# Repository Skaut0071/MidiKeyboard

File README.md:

# MidiKeyboard

Kicad project for Midi piano keyboard

## How?
- Powered by ESP32C3
- USB or Bluethoot conection
- emulates keyboard sending symbols
##
- Has 36 white keys and 25 black keys
- Rechargeble battery
- No app requered

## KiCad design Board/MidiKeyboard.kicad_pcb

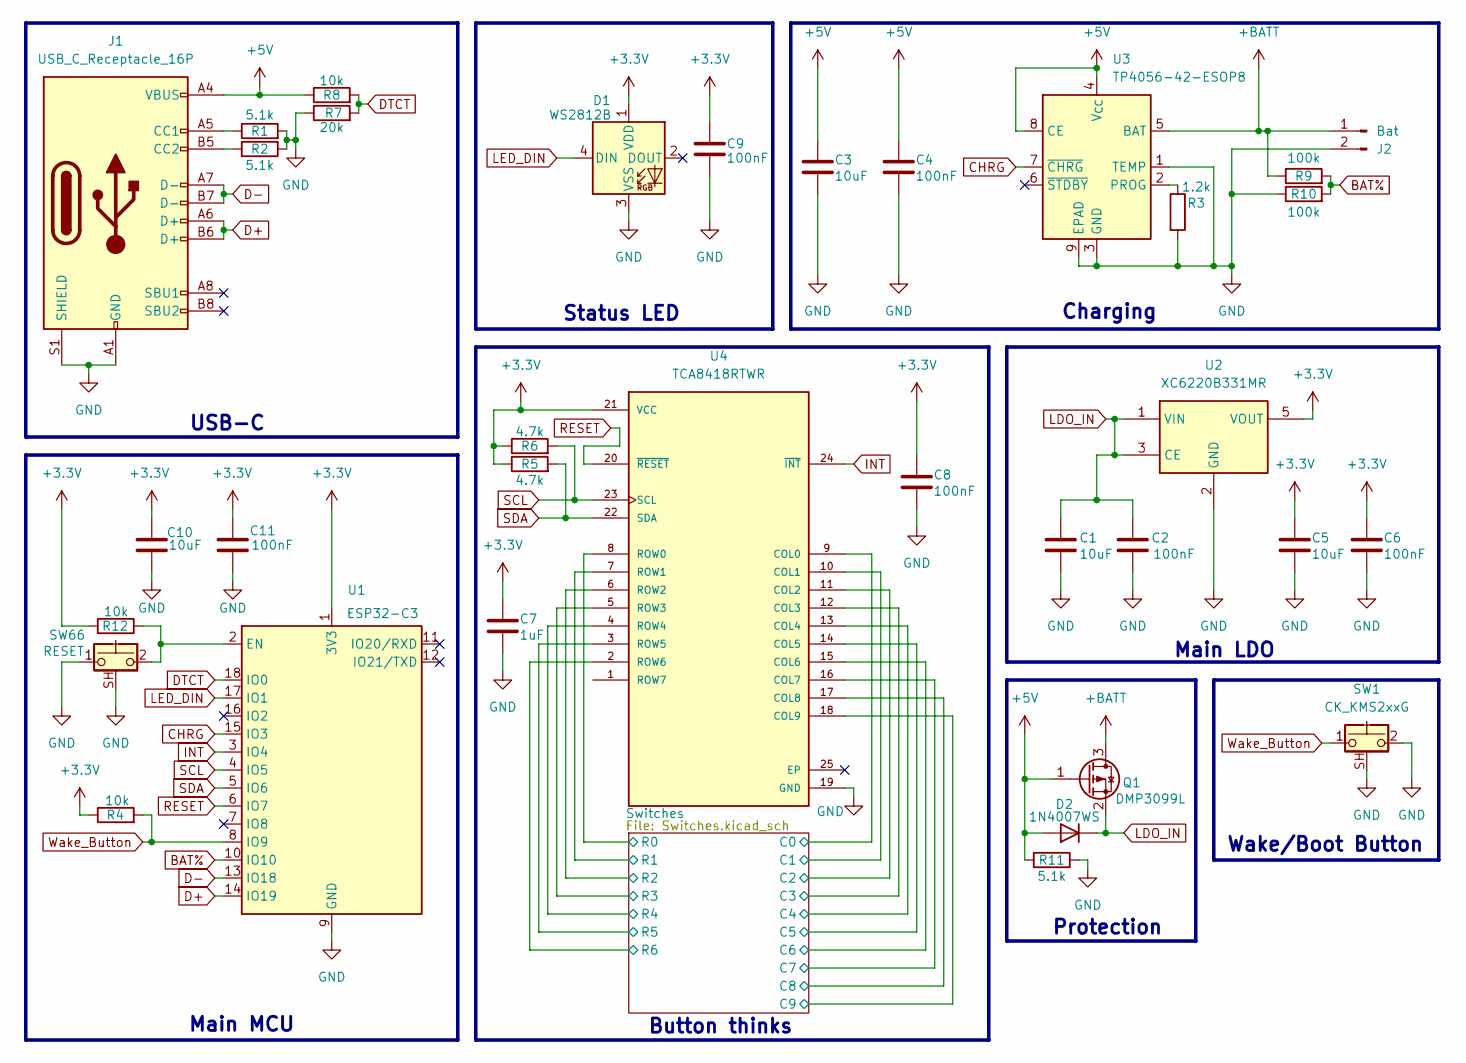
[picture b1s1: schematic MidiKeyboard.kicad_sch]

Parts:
C1, C3, C5, C10: 10uF; C_0402_1005Metric
C2, C4, C6, C8, C9, C11: 100nF; C_0402_1005Metric
C7: 1uF; C_0402_1005Metric
D1: WS2812B; LED_WS2812B_PLCC4_5.0x5.0mm_P3.2mm
D2: 1N4007WS; D_0402_1005Metric
J1: USB_C_Receptacle_16P; USB_C_Receptacle_HCTL_HC-TYPE-C-16P-01A
J2: Bat; JST_PH_B2B-PH-SM4-TB_1x02-1MP_P2.00mm_Vertical
Q1: DMP3099L; SOT-23
R1, R2, R11: 5.1k; R_0402_1005Metric
R3: 1.2k; R_0402_1005Metric
R4, R8, R12: 10k; R_0402_1005Metric
R5, R6: 4.7k; R_0402_1005Metric
R7: 20k; R_0402_1005Metric
R9, R10: 100k; R_0402_1005Metric
SW1: CK_KMS2xxG; SW_SPST_CK_KMS2xxGP
SW66: RESET; SW_SPST_CK_KMS2xxGP
U1: ESP32-C3; ESP32-C3-WROOM-02
U2: XC6220B331MR; SOT-23-5
U3: TP4056-42-ESOP8; SOIC-8-1EP_3.9x4.9mm_P1.27mm_EP2.41x3.3mm_ThermalVias
U4: TCA8418RTWR; QFN50P400X400X80-25N

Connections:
+3.3V: C5.1, C6.1, C7.1, C8.1, C9.1, C10.1, C11.1, D1.1 (VDD), R4.1, R5.1, R6.1, R12.2, U1.1 (3V3), U2.5 (VOUT), U4.21 (VCC)
+5V: C3.1, C4.1, D2.2 (A), J1.A4 (VBUS), J1.A9 (VBUS), J1.B4 (VBUS), J1.B9 (VBUS), Q1.1 (G), R8.1, R11.2, U3.4 (V_{CC}), U3.8 (CE)
+BATT: J2.1, Q1.3 (D), R9.1, U3.5 (BAT)
/Switches/C0: U4.9 (COL0); also elsewhere on the board
/Switches/C1: U4.10 (COL1); also elsewhere on the board
/Switches/C2: U4.11 (COL2); also elsewhere on the board
/Switches/C3: U4.12 (COL3); also elsewhere on the board
/Switches/C4: U4.13 (COL4); also elsewhere on the board
/Switches/C5: U4.14 (COL5); also elsewhere on the board
/Switches/C6: U4.15 (COL6); also elsewhere on the board
/Switches/C7: U4.16 (COL7); also elsewhere on the board
/Switches/C8: U4.17 (COL8); also elsewhere on the board
/Switches/C9: U4.18 (COL9); also elsewhere on the board
/Switches/R0: U4.8 (ROW0); also elsewhere on the board
/Switches/R1: U4.7 (ROW1); also elsewhere on the board
/Switches/R2: U4.6 (ROW2); also elsewhere on the board
/Switches/R3: U4.5 (ROW3); also elsewhere on the board
/Switches/R4: U4.4 (ROW4); also elsewhere on the board
/Switches/R5: U4.3 (ROW5); also elsewhere on the board
/Switches/R6: U4.2 (ROW6); also elsewhere on the board
BAT%: R9.2, R10.2, U1.10 (IO10)
CHRG: U1.15 (IO3), U3.7 (~CHRG)
D+: J1.A6 (D+), J1.B6 (D+), U1.14 (IO19)
D-: J1.A7 (D-), J1.B7 (D-), U1.13 (IO18)
DTCT: R7.2, R8.2, U1.18 (IO0)
GND: C1.2, C2.2, C3.2, C4.2, C5.2, C6.2, C7.2, C8.2, C9.2, C10.2, C11.2, D1.3 (VSS), J1.A1 (GND), J1.A12 (GND), J1.B1 (GND), J1.B12 (GND), J1.S1 (SHIELD), J2.2, R1.2, R2.1, R3.2, R7.1, R10.1, R11.1, SW1.2, SW1.SH (B), SW66.1, SW66.SH (B), U1.9 (GND), U1.19 (GND), U2.2 (GND), U3.1 (TEMP), U3.3 (GND), U3.9 (EPAD), U4.19 (GND)
INT: U1.3 (IO4), U4.24 (~INT)
LDO_IN: C1.1, C2.1, D2.1 (K), Q1.2 (S), U2.1 (VIN), U2.3 (CE)
LED_DIN: D1.4 (DIN), U1.17 (IO1)
unnamed: J1.A5 (CC1), R1.1
unnamed: J1.B5 (CC2), R2.2
unnamed: R12.1, SW66.2, U1.2 (EN)
unnamed: R3.1, U3.2 (PROG)
RESET: U1.6 (IO7), U4.20 (~RESET)
SCL: R6.2, U1.4 (IO5), U4.23 (SCL)
SDA: R5.2, U1.5 (IO6), U4.22 (SDA)
Wake_Button: R4.2, SW1.1, U1.8 (IO9)

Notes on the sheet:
USB-C
Main MCU
Main LDO
Wake/Boot Button
Button thinks
Charging
Status LED
Protection

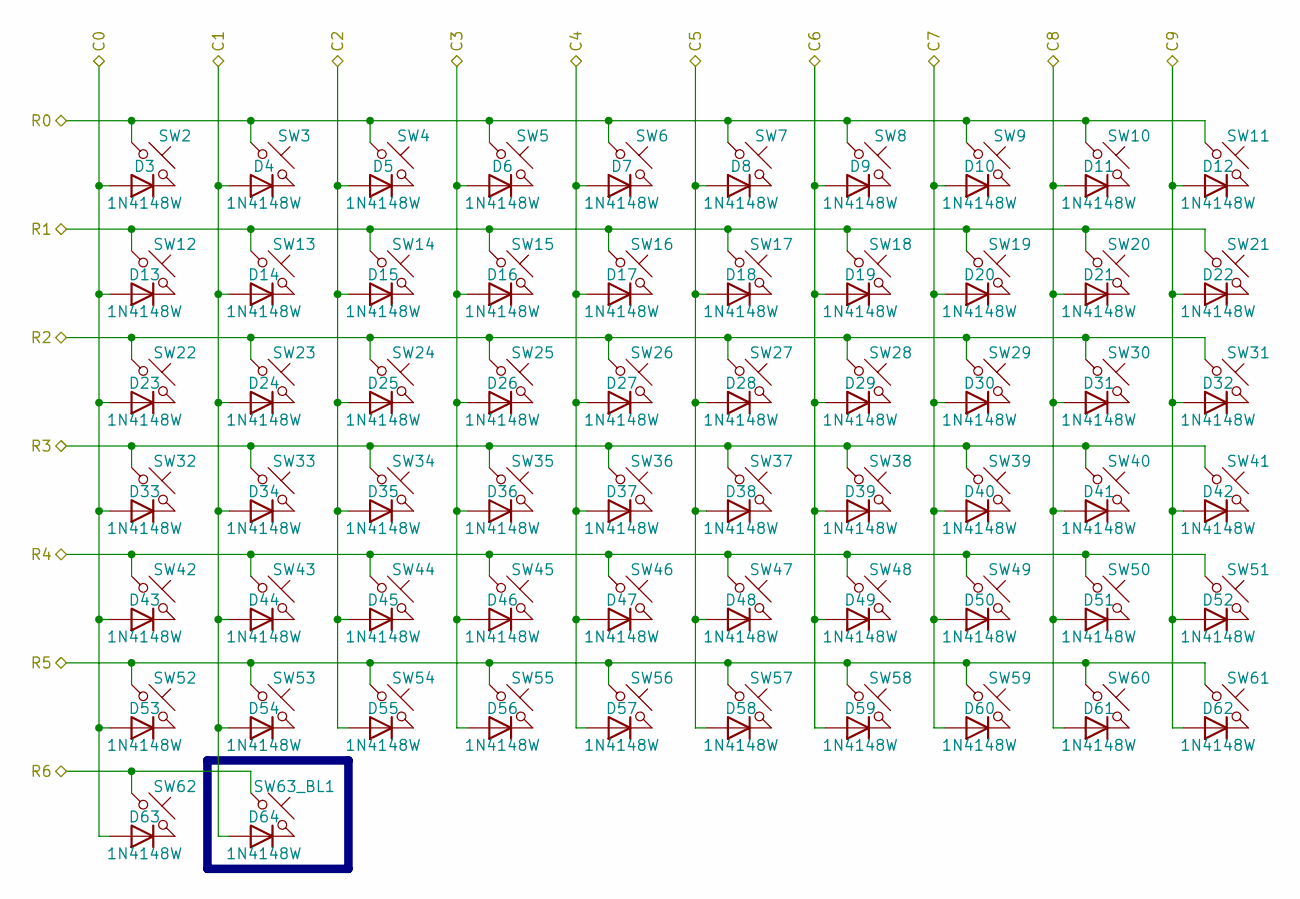
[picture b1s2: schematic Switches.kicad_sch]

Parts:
D3, D4, D5, D6, D7, D8, D9, D10, D11, D12, D13, D14, D15, D16, D17, D18, D19, D20, D21, D22, D23, D24, D25, D26, D27, D28, D29, D30, D31, D32, D33, D34, D35, D36, D37, D38, D39, D40, D41, D42, D43, D44, D45, D46, D47, D48, D49, D50, D51, D52, D53, D54, D55, D56, D57, D58, D59, D60, D61, D62, D63, D64: 1N4148W; D_0402_1005Metric
SW2, SW3, SW4, SW5, SW6, SW7, SW8, SW9, SW10, SW11, SW12, SW13, SW14, SW15, SW16, SW17, SW18, SW19, SW20, SW21, SW22, SW23, SW24, SW25, SW26, SW27, SW28, SW29, SW30, SW31, SW32, SW33, SW34, SW35, SW36, SW37, SW38, SW39, SW40, SW41, SW42, SW43, SW44, SW45, SW46, SW47, SW48, SW49, SW50, SW51, SW52, SW53, SW54, SW55, SW56, SW57, SW58, SW59, SW60, SW61, SW62: SW_Push_45deg; SW_Cherry_MX_1.00u_PCB
SW63_BL1: SW_Push_45deg; SW_SPST_CK_KMS2xxGP

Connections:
/Switches/C0: D3.2 (A), D13.2 (A), D23.2 (A), D33.2 (A), D43.2 (A), D53.2 (A), D63.2 (A); also elsewhere on the board
/Switches/C1: D4.2 (A), D14.2 (A), D24.2 (A), D34.2 (A), D44.2 (A), D54.2 (A), D64.2 (A); also elsewhere on the board
/Switches/C2: D5.2 (A), D15.2 (A), D25.2 (A), D35.2 (A), D45.2 (A), D55.2 (A); also elsewhere on the board
/Switches/C3: D6.2 (A), D16.2 (A), D26.2 (A), D36.2 (A), D46.2 (A), D56.2 (A); also elsewhere on the board
/Switches/C4: D7.2 (A), D17.2 (A), D27.2 (A), D37.2 (A), D47.2 (A), D57.2 (A); also elsewhere on the board
/Switches/C5: D8.2 (A), D18.2 (A), D28.2 (A), D38.2 (A), D48.2 (A), D58.2 (A); also elsewhere on the board
/Switches/C6: D9.2 (A), D19.2 (A), D29.2 (A), D39.2 (A), D49.2 (A), D59.2 (A); also elsewhere on the board
/Switches/C7: D10.2 (A), D20.2 (A), D30.2 (A), D40.2 (A), D50.2 (A), D60.2 (A); also elsewhere on the board
/Switches/C8: D11.2 (A), D21.2 (A), D31.2 (A), D41.2 (A), D51.2 (A), D61.2 (A); also elsewhere on the board
/Switches/C9: D12.2 (A), D22.2 (A), D32.2 (A), D42.2 (A), D52.2 (A), D62.2 (A); also elsewhere on the board
/Switches/R0: SW2.1, SW3.1, SW4.1, SW5.1, SW6.1, SW7.1, SW8.1, SW9.1, SW10.1, SW11.1; also elsewhere on the board
/Switches/R1: SW12.1, SW13.1, SW14.1, SW15.1, SW16.1, SW17.1, SW18.1, SW19.1, SW20.1, SW21.1; also elsewhere on the board
/Switches/R2: SW22.1, SW23.1, SW24.1, SW25.1, SW26.1, SW27.1, SW28.1, SW29.1, SW30.1, SW31.1; also elsewhere on the board
/Switches/R3: SW32.1, SW33.1, SW34.1, SW35.1, SW36.1, SW37.1, SW38.1, SW39.1, SW40.1, SW41.1; also elsewhere on the board
/Switches/R4: SW42.1, SW43.1, SW44.1, SW45.1, SW46.1, SW47.1, SW48.1, SW49.1, SW50.1, SW51.1; also elsewhere on the board
/Switches/R5: SW52.1, SW53.1, SW54.1, SW55.1, SW56.1, SW57.1, SW58.1, SW59.1, SW60.1, SW61.1; also elsewhere on the board
/Switches/R6: SW62.1, SW63_BL1.1; also elsewhere on the board
unnamed: D3.1 (K), SW2.2
unnamed: D4.1 (K), SW3.2
unnamed: D5.1 (K), SW4.2
unnamed: D6.1 (K), SW5.2
unnamed: D7.1 (K), SW6.2
unnamed: D8.1 (K), SW7.2
unnamed: D9.1 (K), SW8.2
unnamed: D10.1 (K), SW9.2
unnamed: D11.1 (K), SW10.2
unnamed: D12.1 (K), SW11.2
unnamed: D13.1 (K), SW12.2
unnamed: D14.1 (K), SW13.2
unnamed: D15.1 (K), SW14.2
unnamed: D16.1 (K), SW15.2
unnamed: D17.1 (K), SW16.2
unnamed: D18.1 (K), SW17.2
unnamed: D19.1 (K), SW18.2
unnamed: D20.1 (K), SW19.2
unnamed: D21.1 (K), SW20.2
unnamed: D22.1 (K), SW21.2
unnamed: D23.1 (K), SW22.2
unnamed: D24.1 (K), SW23.2
unnamed: D25.1 (K), SW24.2
unnamed: D26.1 (K), SW25.2
unnamed: D27.1 (K), SW26.2
unnamed: D28.1 (K), SW27.2
unnamed: D29.1 (K), SW28.2
unnamed: D30.1 (K), SW29.2
unnamed: D31.1 (K), SW30.2
unnamed: D32.1 (K), SW31.2
unnamed: D33.1 (K), SW32.2
unnamed: D34.1 (K), SW33.2
unnamed: D35.1 (K), SW34.2
unnamed: D36.1 (K), SW35.2
unnamed: D37.1 (K), SW36.2
unnamed: D38.1 (K), SW37.2
unnamed: D39.1 (K), SW38.2
unnamed: D40.1 (K), SW39.2
unnamed: D41.1 (K), SW40.2
unnamed: D42.1 (K), SW41.2
unnamed: D43.1 (K), SW42.2
unnamed: D44.1 (K), SW43.2
unnamed: D45.1 (K), SW44.2
unnamed: D46.1 (K), SW45.2
unnamed: D47.1 (K), SW46.2
unnamed: D48.1 (K), SW47.2
unnamed: D49.1 (K), SW48.2
unnamed: D50.1 (K), SW49.2
unnamed: D51.1 (K), SW50.2
unnamed: D52.1 (K), SW51.2
unnamed: D53.1 (K), SW52.2
unnamed: D54.1 (K), SW53.2
unnamed: D55.1 (K), SW54.2
unnamed: D56.1 (K), SW55.2
unnamed: D57.1 (K), SW56.2
unnamed: D58.1 (K), SW57.2
unnamed: D59.1 (K), SW58.2
unnamed: D60.1 (K), SW59.2
unnamed: D61.1 (K), SW60.2
unnamed: D62.1 (K), SW61.2
unnamed: D63.1 (K), SW62.2
unnamed: D64.1 (K), SW63_BL1.2

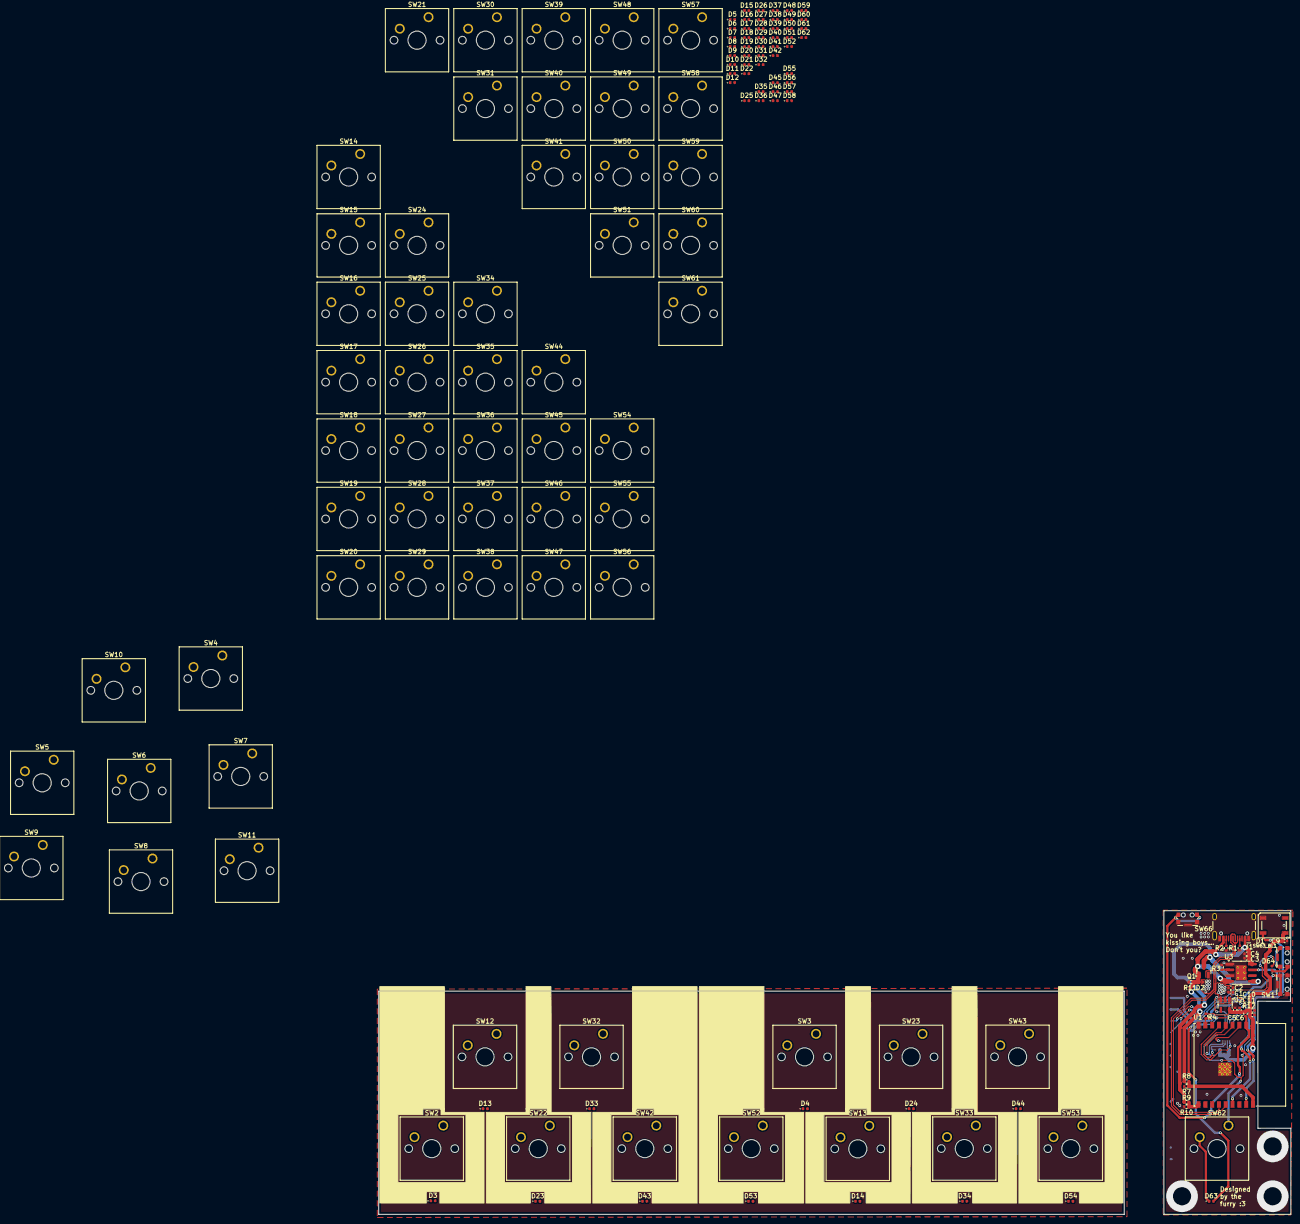
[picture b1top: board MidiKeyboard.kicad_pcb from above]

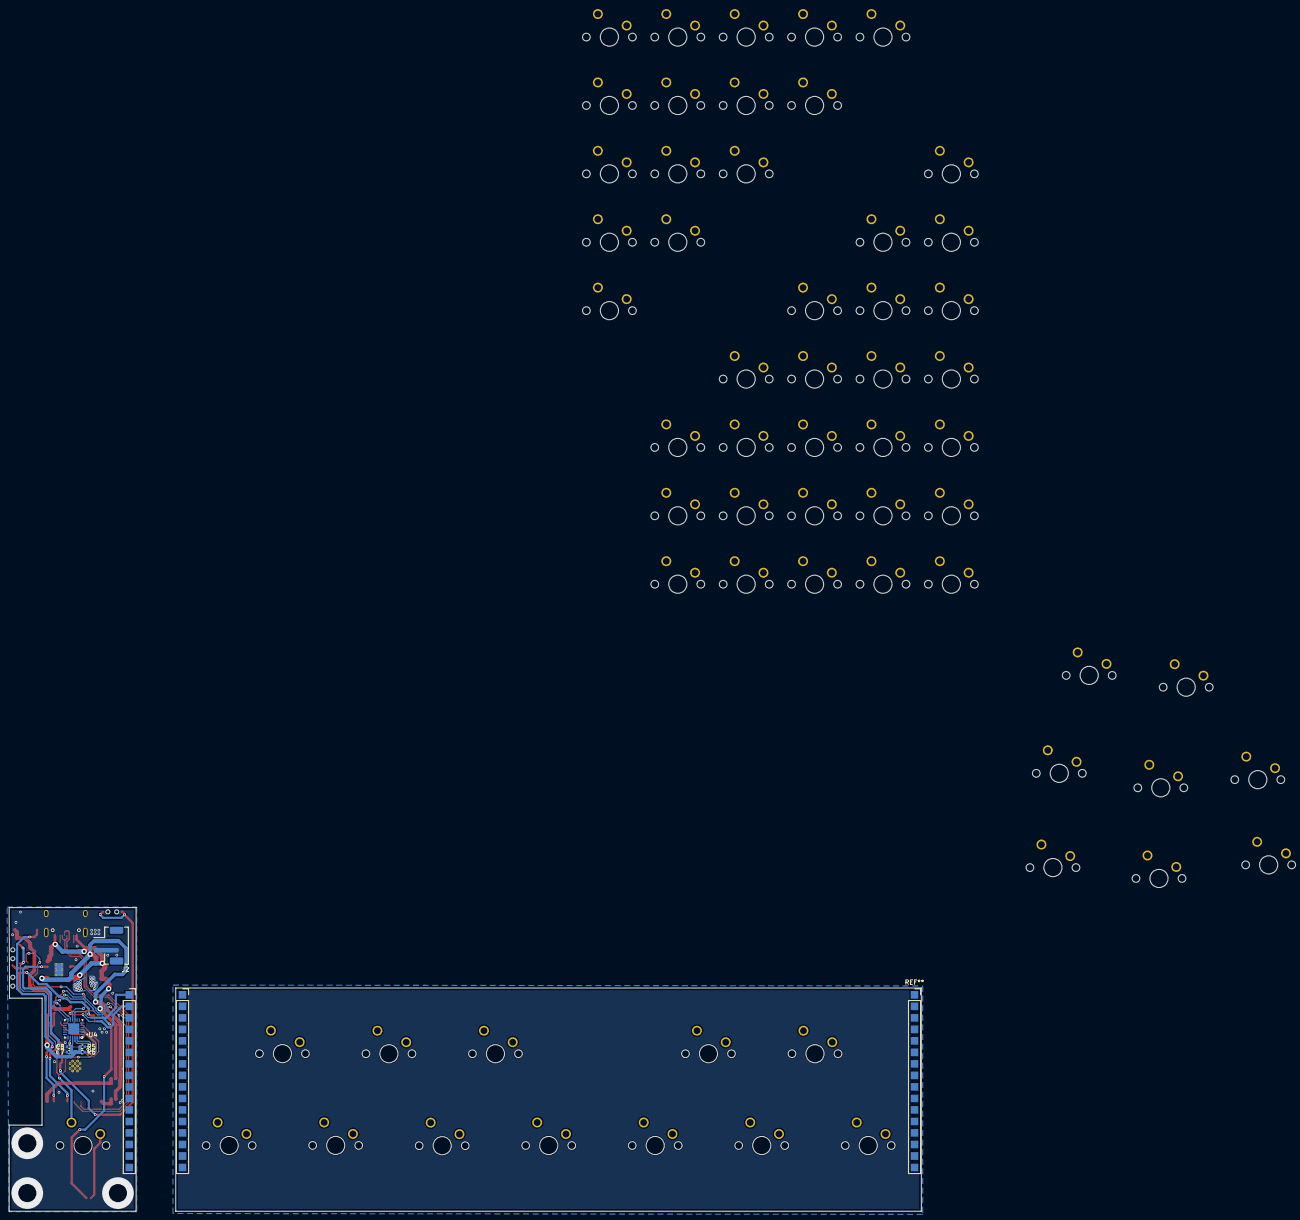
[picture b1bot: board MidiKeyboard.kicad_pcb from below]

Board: 2 copper layers, 201.2 x 67.0 mm, 158 parts (6 on the bottom side), 99 nets.

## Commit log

2026-03-15 Expand README with project details
    Added project details including power source, connection types, key count, battery, and app requirements.
2026-03-15 Raw Schema - NON FINISHED
2026-03-15 Complete Schema + Starting PCB
    Anythink may be changed
2026-03-16 Main Board conections
2026-04-05 Uprava pro jednodusi kontrolu
